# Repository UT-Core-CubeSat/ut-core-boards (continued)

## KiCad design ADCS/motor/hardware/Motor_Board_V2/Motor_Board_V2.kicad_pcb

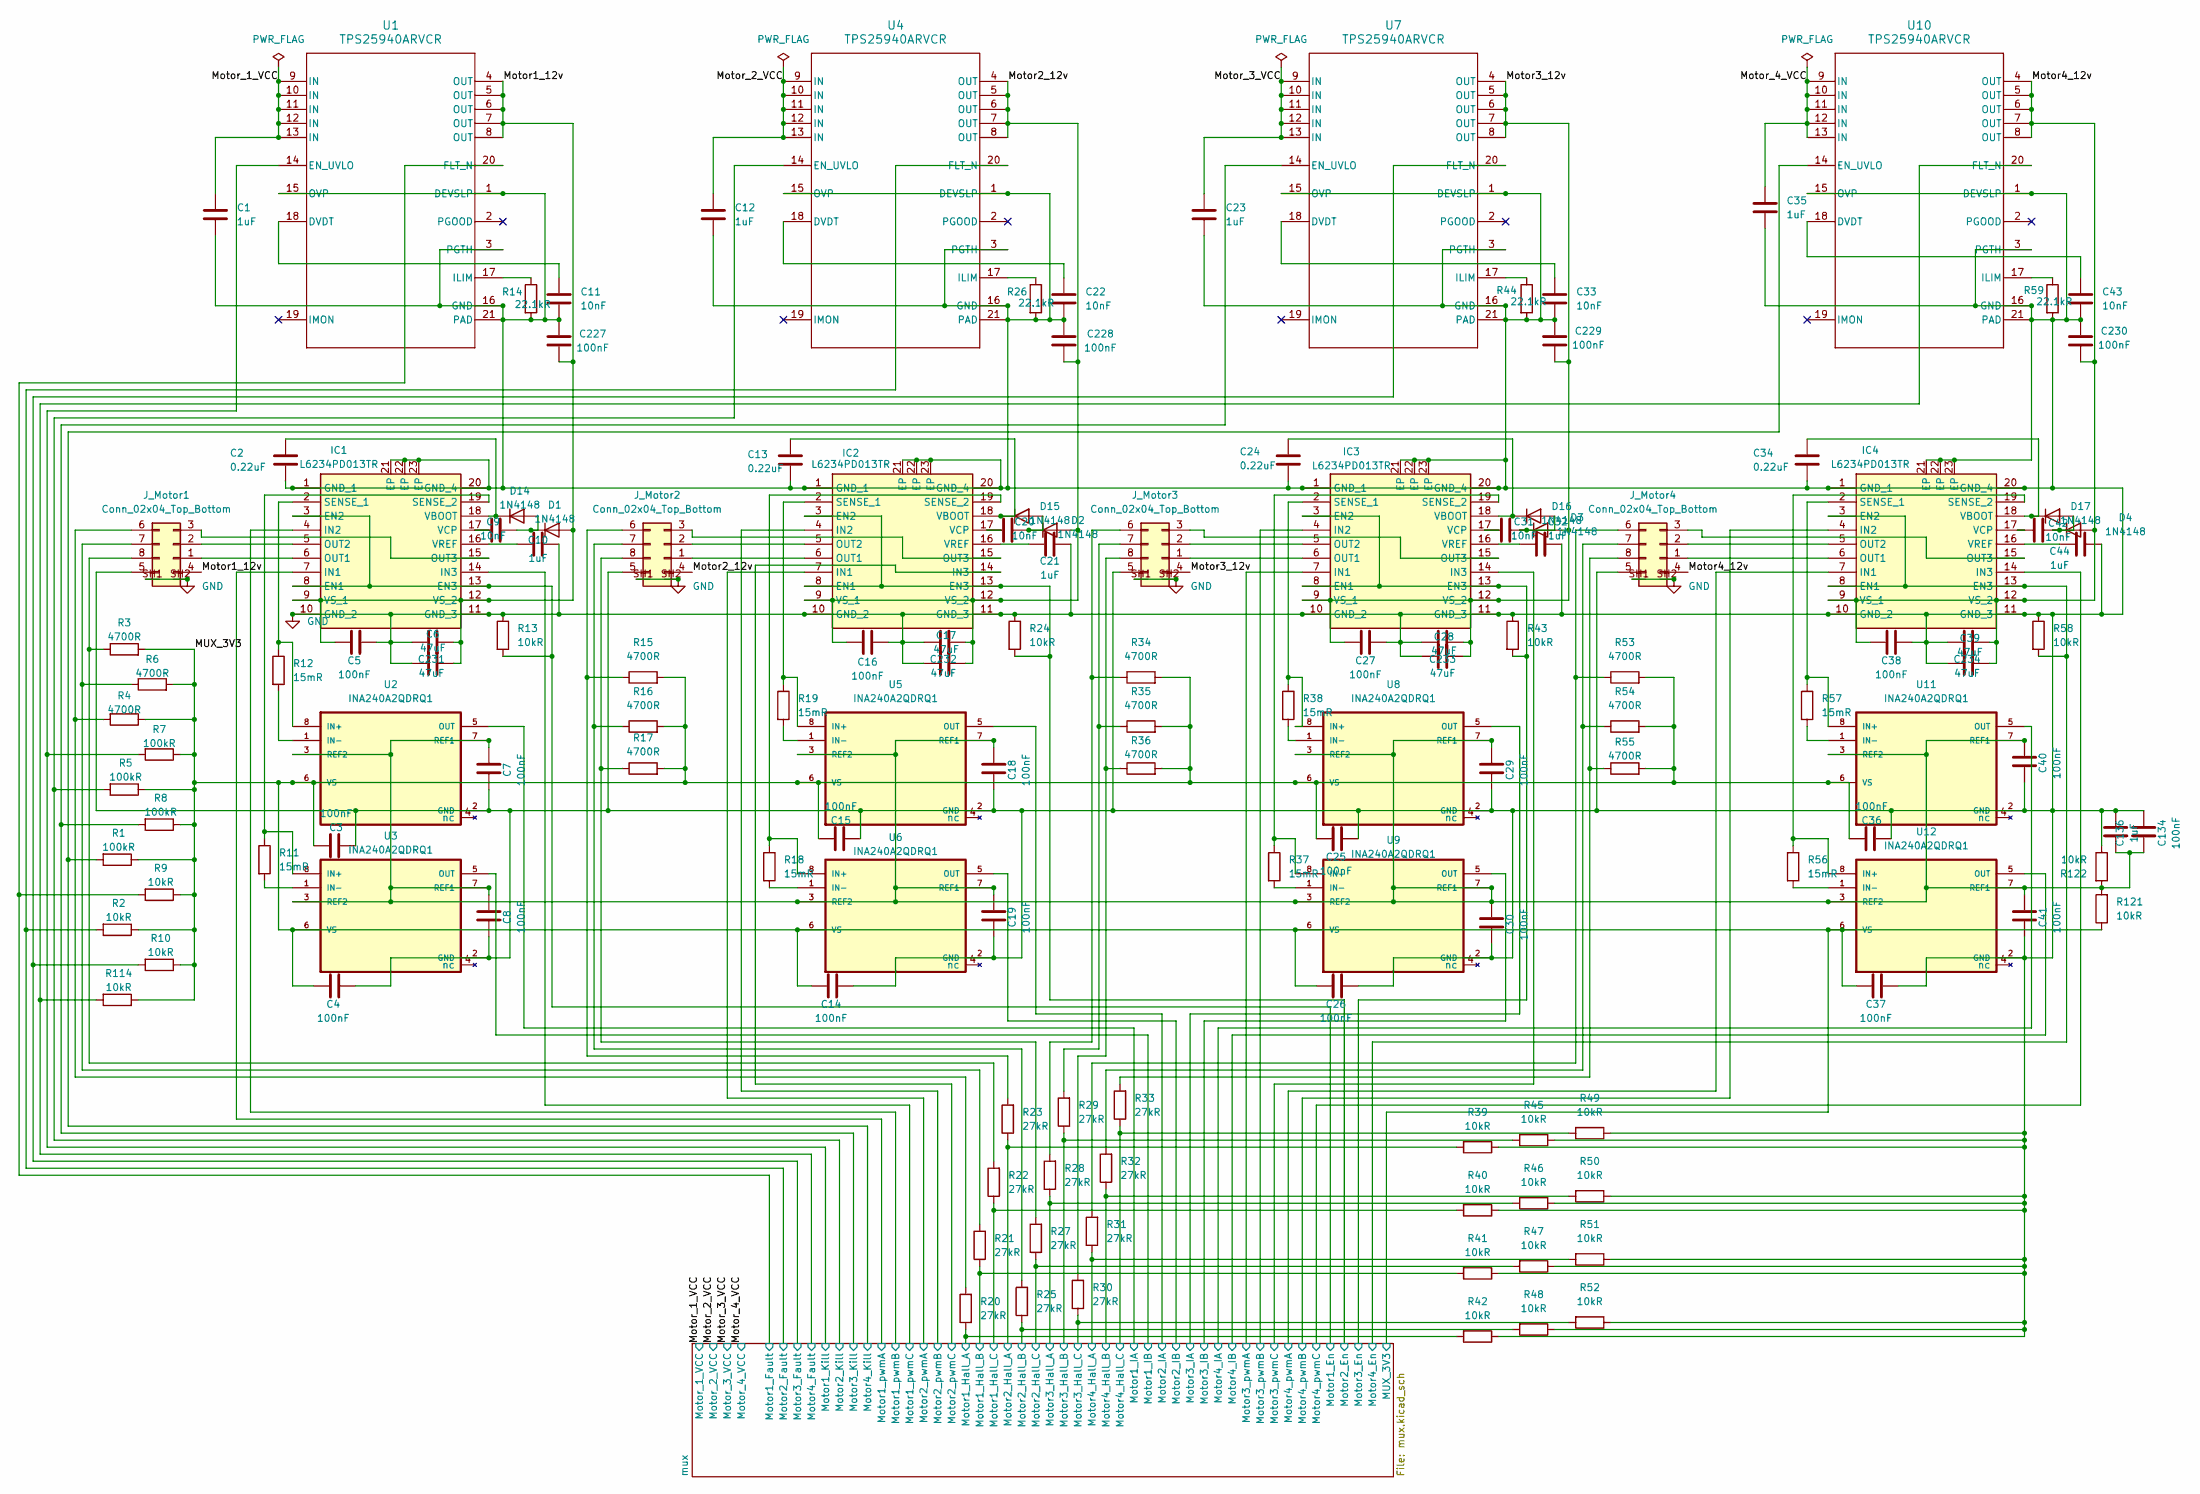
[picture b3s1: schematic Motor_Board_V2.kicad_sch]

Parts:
C1, C10, C12, C21, C23, C32, C35, C44, C136: 1uF; C_0603_1608Metric
C2, C13, C24, C34: 0.22uF; C_0603_1608Metric
C3, C4, C5, C7, C8, C14, C15, C16, C18, C19, C25, C26, C27, C29, C30, C36, C37, C38, C40, C41, C134, C227, C228, C229, C230: 100nF; C_0603_1608Metric
C6, C17, C28, C39, C231, C232, C233, C234: 47uF; C_1210_3225Metric
C9, C20, C31, C42: 10nF; C_0603_1608Metric_Pad1.08x0.95mm_HandSolder
C11, C22, C33, C43: 10nF; C_0603_1608Metric
D1, D2, D3, D4, D14, D15, D16, D17: 1N4148; D_SOD-523
IC1, IC2, IC3, IC4: L6234PD013TR; SOIC127P1420X360-21N; Manufacturer_Part_Number L6234PD; Mouser Part Number 511-L6234PD
J_Motor1, J_Motor2, J_Motor3, J_Motor4: Conn_02x04_Top_Bottom; AMPHENOL_SFW8S-2STME1LF
R1, R5, R7, R8: 100kR; R_0805_2012Metric
R2, R9, R10, R13, R24, R39, R40, R41, R42, R43, R45, R46, R47, R48, R49, R50, R51, R52, R58, R114, R121, R122: 10kR; R_0805_2012Metric
R3, R4, R6, R15, R16, R17, R34, R35, R36, R53, R54, R55: 4700R; R_0603_1608Metric
R11, R12, R18, R19, R37, R38, R56, R57: 15mR; R_2512_6332Metric
R14, R26, R44, R59: 22.1kR; R_0805_2012Metric
R20, R21, R22, R23, R25, R27, R28, R29, R30, R31, R32, R33: 27kR; R_0805_2012Metric
U1, U4, U7, U10: TPS25940ARVCR; RVC0020A
U2, U3, U5, U6, U8, U9, U11, U12: INA240A2QDRQ1; SOIC127P599X175-8N

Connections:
/MUX_3V3: C3.2, C4.1, C14.1, C15.2, C25.1, C26.1, C36.2, C37.1, R1.1, R2.1, R3.2, R4.1, R5.1, R6.2, R7.1, R8.1, R9.1, R10.1, R15.2, R16.2, R17.2, R34.2, R35.2, R36.2, R53.2, R54.2, R55.2, R114.1, R121.1, U2.6 (VS), U3.6 (VS), U5.6 (VS), U6.6 (VS), U8.6 (VS), U9.6 (VS), U11.6 (VS), U12.6 (VS); also elsewhere on the board
/Motor1_12v: C5.1, C6.1, C227.1, C231.1, D1.2 (A), IC1.9 (VS_1), IC1.12 (VS_2), J_Motor1.4 (Pin_8), U1.4 (OUT), U1.5 (OUT), U1.6 (OUT), U1.7 (OUT), U1.8 (OUT)
/Motor2_12v: C16.1, C17.1, C228.1, C232.1, D2.2 (A), IC2.9 (VS_1), IC2.12 (VS_2), J_Motor2.4 (Pin_8), U4.4 (OUT), U4.5 (OUT), U4.6 (OUT), U4.7 (OUT), U4.8 (OUT)
/Motor3_12v: C27.1, C28.1, C229.1, C233.1, D3.2 (A), IC3.9 (VS_1), IC3.12 (VS_2), J_Motor3.4 (Pin_8), U7.4 (OUT), U7.5 (OUT), U7.6 (OUT), U7.7 (OUT), U7.8 (OUT)
/Motor4_12v: C38.1, C39.1, C230.1, C234.1, D4.2 (A), IC4.9 (VS_1), IC4.12 (VS_2), J_Motor4.4 (Pin_8), U10.4 (OUT), U10.5 (OUT), U10.6 (OUT), U10.7 (OUT), U10.8 (OUT)
/Motor_1_VCC: C1.1, U1.9 (IN), U1.10 (IN), U1.11 (IN), U1.12 (IN), U1.13 (IN); also elsewhere on the board
/Motor_2_VCC: C12.1, U4.9 (IN), U4.10 (IN), U4.11 (IN), U4.12 (IN), U4.13 (IN); also elsewhere on the board
/Motor_3_VCC: C23.1, U7.9 (IN), U7.10 (IN), U7.11 (IN), U7.12 (IN), U7.13 (IN); also elsewhere on the board
/Motor_4_VCC: C35.1, U10.9 (IN), U10.10 (IN), U10.11 (IN), U10.12 (IN), U10.13 (IN); also elsewhere on the board
/mux/Motor1_En: IC1.3 (EN2), IC1.8 (EN1), IC1.13 (EN3), R13.2; also elsewhere on the board
/mux/Motor1_Fault: R9.2, U1.20 (FLT_N); also elsewhere on the board
/mux/Motor1_Hall_A: R20.1, R42.2; also elsewhere on the board
/mux/Motor1_Hall_B: R21.1, R41.2; also elsewhere on the board
/mux/Motor1_Hall_C: R22.1, R40.2; also elsewhere on the board
/mux/Motor1_IA: U2.5 (OUT); also elsewhere on the board
/mux/Motor1_IB: U3.5 (OUT); also elsewhere on the board
/mux/Motor1_Kill: R7.2, U1.14 (EN_UVLO); also elsewhere on the board
/mux/Motor1_pwmA: IC1.7 (IN1); also elsewhere on the board
/mux/Motor1_pwmB: IC1.4 (IN2); also elsewhere on the board
/mux/Motor1_pwmC: IC1.14 (IN3); also elsewhere on the board
/mux/Motor2_En: IC2.3 (EN2), IC2.8 (EN1), IC2.13 (EN3), R24.2; also elsewhere on the board
/mux/Motor2_Fault: R2.2, U4.20 (FLT_N); also elsewhere on the board
/mux/Motor2_Hall_A: R23.1, R39.2; also elsewhere on the board
/mux/Motor2_Hall_B: R25.1, R48.2; also elsewhere on the board
/mux/Motor2_Hall_C: R27.1, R47.2; also elsewhere on the board
/mux/Motor2_IA: U5.5 (OUT); also elsewhere on the board
/mux/Motor2_IB: U6.5 (OUT); also elsewhere on the board
/mux/Motor2_Kill: R5.2, U4.14 (EN_UVLO); also elsewhere on the board
/mux/Motor2_pwmA: IC2.7 (IN1); also elsewhere on the board
/mux/Motor2_pwmB: IC2.4 (IN2); also elsewhere on the board
/mux/Motor2_pwmC: IC2.14 (IN3); also elsewhere on the board
/mux/Motor3_En: IC3.3 (EN2), IC3.8 (EN1), IC3.13 (EN3), R43.2; also elsewhere on the board
/mux/Motor3_Fault: R10.2, U7.20 (FLT_N); also elsewhere on the board
/mux/Motor3_Hall_A: R28.1, R46.2; also elsewhere on the board
/mux/Motor3_Hall_B: R29.1, R45.2; also elsewhere on the board
/mux/Motor3_Hall_C: R30.1, R52.2; also elsewhere on the board
/mux/Motor3_IA: U8.5 (OUT); also elsewhere on the board
/mux/Motor3_IB: U9.5 (OUT); also elsewhere on the board
/mux/Motor3_Kill: R8.2, U7.14 (EN_UVLO); also elsewhere on the board
/mux/Motor3_pwmA: IC3.7 (IN1); also elsewhere on the board
/mux/Motor3_pwmB: IC3.4 (IN2); also elsewhere on the board
/mux/Motor3_pwmC: IC3.14 (IN3); also elsewhere on the board
/mux/Motor4_En: IC4.3 (EN2), IC4.8 (EN1), IC4.13 (EN3), R58.2; also elsewhere on the board
/mux/Motor4_Fault: R114.2, U10.20 (FLT_N); also elsewhere on the board
/mux/Motor4_Hall_A: R31.1, R51.2; also elsewhere on the board
/mux/Motor4_Hall_B: R32.1, R50.2; also elsewhere on the board
/mux/Motor4_Hall_C: R33.1, R49.2; also elsewhere on the board
/mux/Motor4_IA: U11.5 (OUT); also elsewhere on the board
/mux/Motor4_IB: U12.5 (OUT); also elsewhere on the board
/mux/Motor4_Kill: R1.2, U10.14 (EN_UVLO); also elsewhere on the board
/mux/Motor4_pwmA: IC4.7 (IN1); also elsewhere on the board
/mux/Motor4_pwmB: IC4.4 (IN2); also elsewhere on the board
/mux/Motor4_pwmC: IC4.14 (IN3); also elsewhere on the board
unnamed: C9.2, D1.1 (K), D14.2 (A)
unnamed: C2.1, D14.1 (K), IC1.18 (VBOOT)
unnamed: C20.2, D2.1 (K), D15.2 (A)
unnamed: C13.1, D15.1 (K), IC2.18 (VBOOT)
unnamed: C31.2, D3.1 (K), D16.2 (A)
unnamed: C24.1, D16.1 (K), IC3.18 (VBOOT)
unnamed: C42.2, D4.1 (K), D17.2 (A)
unnamed: C34.1, D17.1 (K), IC4.18 (VBOOT)
unnamed: IC1.6 (OUT1), J_Motor1.1 (Pin_7)
unnamed: IC1.5 (OUT2), J_Motor1.2 (Pin_6)
unnamed: IC1.15 (OUT3), J_Motor1.3 (Pin_5)
unnamed: IC1.2 (SENSE_1), R12.1, U2.8 (IN+)
unnamed: IC1.19 (SENSE_2), R11.1, U3.8 (IN+)
unnamed: C9.1, IC1.17 (VCP)
unnamed: C10.1, IC1.16 (VREF)
unnamed: IC2.6 (OUT1), J_Motor2.1 (Pin_7)
unnamed: IC2.5 (OUT2), J_Motor2.2 (Pin_6)
unnamed: IC2.15 (OUT3), J_Motor2.3 (Pin_5)
unnamed: IC2.2 (SENSE_1), R19.1, U5.8 (IN+)
unnamed: IC2.19 (SENSE_2), R18.1, U6.8 (IN+)
unnamed: C20.1, IC2.17 (VCP)
unnamed: C21.1, IC2.16 (VREF)
unnamed: IC3.6 (OUT1), J_Motor3.1 (Pin_7)
unnamed: IC3.5 (OUT2), J_Motor3.2 (Pin_6)
unnamed: IC3.15 (OUT3), J_Motor3.3 (Pin_5)
unnamed: IC3.2 (SENSE_1), R38.1, U8.8 (IN+)
unnamed: IC3.19 (SENSE_2), R37.1, U9.8 (IN+)
unnamed: C31.1, IC3.17 (VCP)
unnamed: C32.1, IC3.16 (VREF)
unnamed: IC4.6 (OUT1), J_Motor4.1 (Pin_7)
unnamed: IC4.5 (OUT2), J_Motor4.2 (Pin_6)
unnamed: IC4.15 (OUT3), J_Motor4.3 (Pin_5)
unnamed: IC4.2 (SENSE_1), R57.1, U11.8 (IN+)
unnamed: IC4.19 (SENSE_2), R56.1, U12.8 (IN+)
unnamed: C42.1, IC4.17 (VCP)
unnamed: C44.1, IC4.16 (VREF)
unnamed: J_Motor1.6 (Pin_1), R4.2, R20.2
unnamed: J_Motor1.7 (Pin_2), R6.1, R21.2
unnamed: J_Motor1.8 (Pin_3), R3.1, R22.2
unnamed: J_Motor2.6 (Pin_1), R15.1, R23.2
unnamed: J_Motor2.7 (Pin_2), R16.1, R25.2
unnamed: J_Motor2.8 (Pin_3), R17.1, R27.2
unnamed: J_Motor3.6 (Pin_1), R28.2, R34.1
unnamed: J_Motor3.7 (Pin_2), R29.2, R35.1
unnamed: J_Motor3.8 (Pin_3), R30.2, R36.1
unnamed: J_Motor4.6 (Pin_1), R31.2, R53.1
unnamed: J_Motor4.7 (Pin_2), R32.2, R54.1
unnamed: J_Motor4.8 (Pin_3), R33.2, R55.1
unnamed: C11.1, U1.18 (DVDT)
unnamed: R14.1, U1.17 (ILIM)
unnamed: R12.2, U2.1 (IN-)
unnamed: R11.2, U3.1 (IN-)
unnamed: C22.1, U4.18 (DVDT)
unnamed: R26.1, U4.17 (ILIM)
unnamed: R19.2, U5.1 (IN-)
unnamed: R18.2, U6.1 (IN-)
unnamed: C33.1, U7.18 (DVDT)
unnamed: R44.1, U7.17 (ILIM)
unnamed: R38.2, U8.1 (IN-)
unnamed: R37.2, U9.1 (IN-)
unnamed: C43.1, U10.18 (DVDT)
unnamed: R59.1, U10.17 (ILIM)
unnamed: R57.2, U11.1 (IN-)
unnamed: C7.2, C8.2, C18.2, C19.2, C29.2, C30.2, C40.2, C41.2, C134.1, C136.1, R121.2, R122.2, U2.3 (REF2), U2.7 (REF1), U3.3 (REF2), U3.7 (REF1), U5.3 (REF2), U5.7 (REF1), U6.3 (REF2), U6.7 (REF1), U8.3 (REF2), U8.7 (REF1), U9.3 (REF2), U9.7 (REF1), U11.3 (REF2), U11.7 (REF1), U12.3 (REF2), U12.7 (REF1)
unnamed: R56.2, U12.1 (IN-)

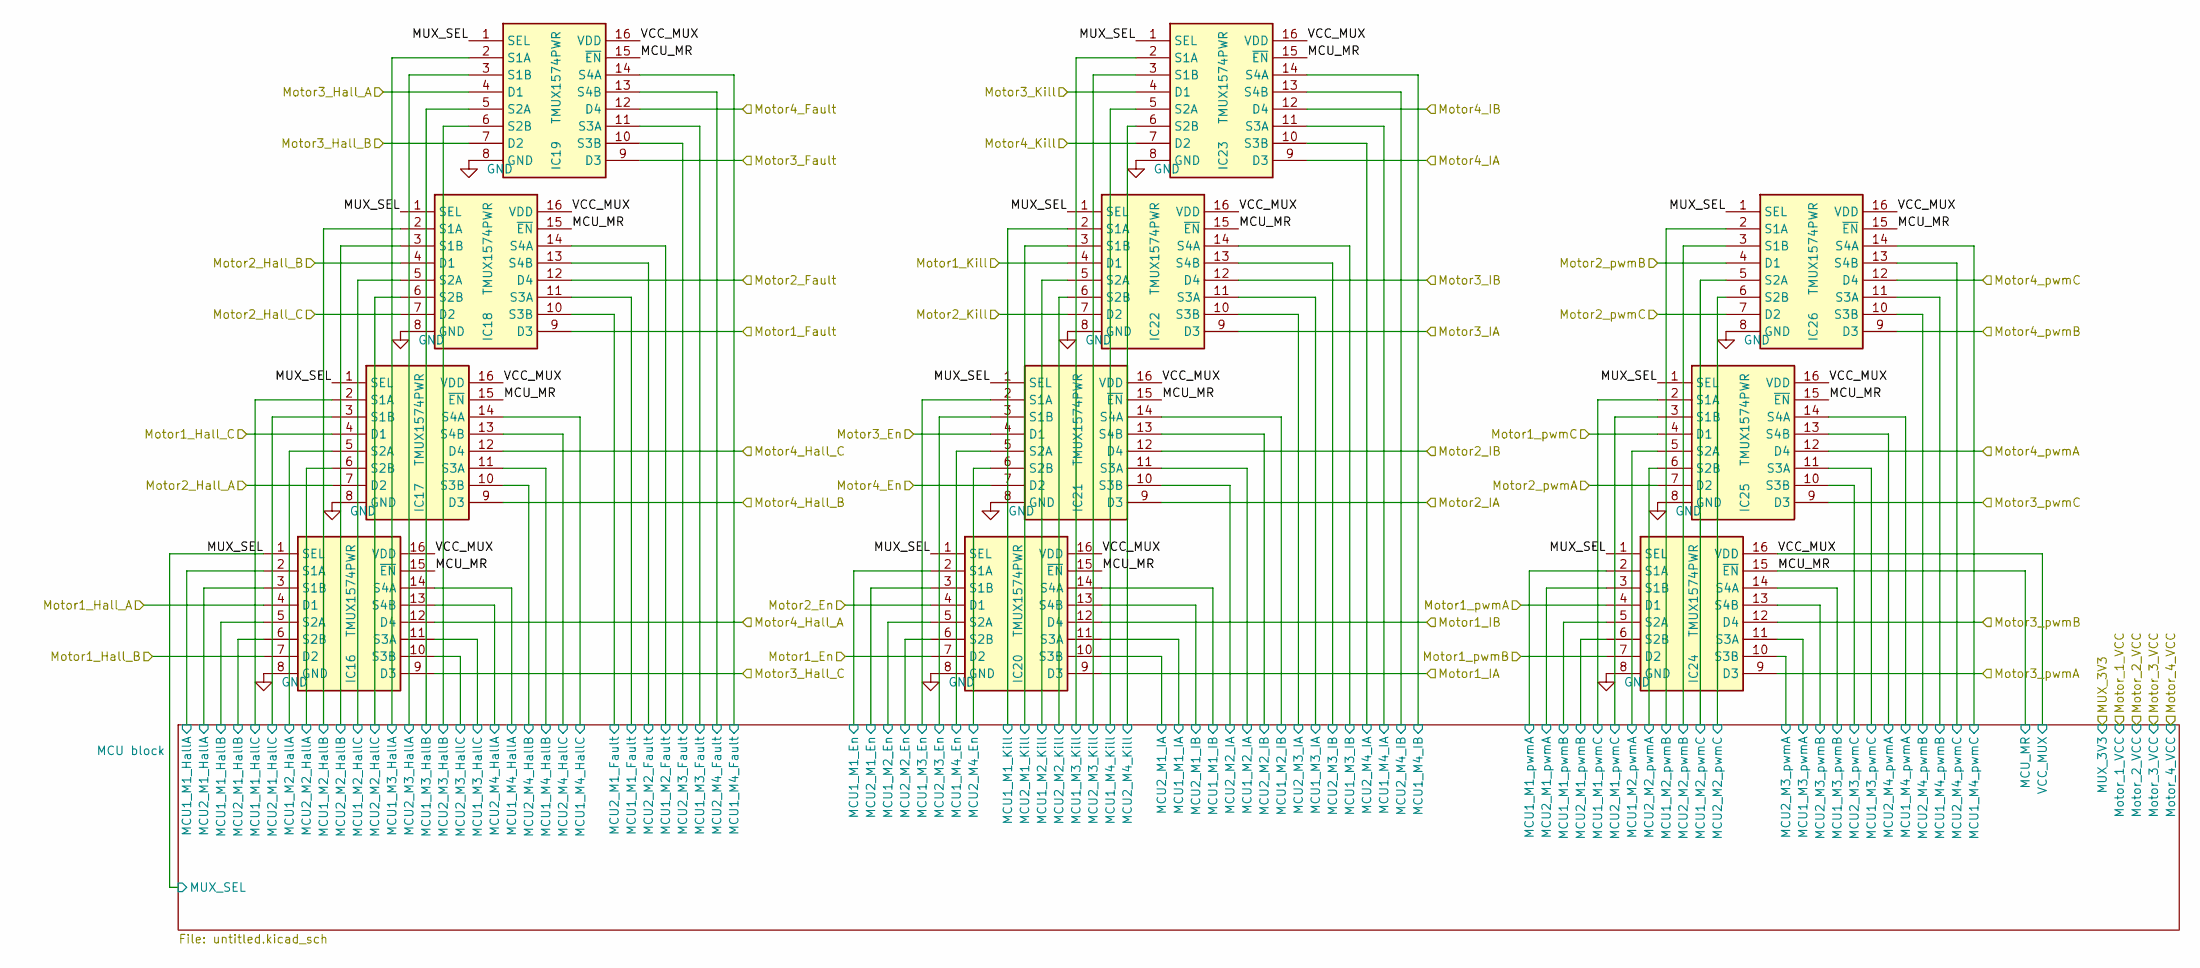
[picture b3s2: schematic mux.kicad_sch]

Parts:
IC16, IC17, IC18, IC19, IC20, IC21, IC22, IC23, IC24, IC25, IC26: TMUX1574PWR; Mouser Part Number 595-TMUX1574PWR

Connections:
/mux/MCU block/MCU1_M1_En: IC20.3 (S1B); also elsewhere on the board
/mux/MCU block/MCU1_M1_Fault: IC18.11 (S3A); also elsewhere on the board
/mux/MCU block/MCU1_M1_HallA: IC16.2 (S1A); also elsewhere on the board
/mux/MCU block/MCU1_M1_HallB: IC16.5 (S2A); also elsewhere on the board
/mux/MCU block/MCU1_M1_HallC: IC17.2 (S1A); also elsewhere on the board
/mux/MCU block/MCU1_M1_IA: IC20.10 (S3B); also elsewhere on the board
/mux/MCU block/MCU1_M1_IB: IC20.13 (S4B); also elsewhere on the board
/mux/MCU block/MCU1_M1_Kill: IC22.3 (S1B); also elsewhere on the board
/mux/MCU block/MCU1_M1_pwmA: IC24.2 (S1A); also elsewhere on the board
/mux/MCU block/MCU1_M1_pwmB: IC24.5 (S2A); also elsewhere on the board
/mux/MCU block/MCU1_M1_pwmC: IC25.2 (S1A); also elsewhere on the board
/mux/MCU block/MCU1_M2_En: IC20.6 (S2B); also elsewhere on the board
/mux/MCU block/MCU1_M2_Fault: IC18.14 (S4A); also elsewhere on the board
/mux/MCU block/MCU1_M2_HallA: IC17.5 (S2A); also elsewhere on the board
/mux/MCU block/MCU1_M2_HallB: IC18.2 (S1A); also elsewhere on the board
/mux/MCU block/MCU1_M2_HallC: IC18.5 (S2A); also elsewhere on the board
/mux/MCU block/MCU1_M2_IA: IC21.10 (S3B); also elsewhere on the board
/mux/MCU block/MCU1_M2_IB: IC21.13 (S4B); also elsewhere on the board
/mux/MCU block/MCU1_M2_Kill: IC22.6 (S2B); also elsewhere on the board
/mux/MCU block/MCU1_M2_pwmA: IC25.5 (S2A); also elsewhere on the board
/mux/MCU block/MCU1_M2_pwmB: IC26.2 (S1A); also elsewhere on the board
/mux/MCU block/MCU1_M2_pwmC: IC26.5 (S2A); also elsewhere on the board
/mux/MCU block/MCU1_M3_En: IC21.3 (S1B); also elsewhere on the board
/mux/MCU block/MCU1_M3_Fault: IC19.11 (S3A); also elsewhere on the board
/mux/MCU block/MCU1_M3_HallA: IC19.2 (S1A); also elsewhere on the board
/mux/MCU block/MCU1_M3_HallB: IC19.5 (S2A); also elsewhere on the board
/mux/MCU block/MCU1_M3_HallC: IC16.10 (S3B); also elsewhere on the board
/mux/MCU block/MCU1_M3_IA: IC22.10 (S3B); also elsewhere on the board
/mux/MCU block/MCU1_M3_IB: IC22.13 (S4B); also elsewhere on the board
/mux/MCU block/MCU1_M3_Kill: IC23.3 (S1B); also elsewhere on the board
/mux/MCU block/MCU1_M3_pwmA: IC24.10 (S3B); also elsewhere on the board
/mux/MCU block/MCU1_M3_pwmB: IC24.13 (S4B); also elsewhere on the board
/mux/MCU block/MCU1_M3_pwmC: IC25.10 (S3B); also elsewhere on the board
/mux/MCU block/MCU1_M4_En: IC21.6 (S2B); also elsewhere on the board
/mux/MCU block/MCU1_M4_Fault: IC19.14 (S4A); also elsewhere on the board
/mux/MCU block/MCU1_M4_HallA: IC16.13 (S4B); also elsewhere on the board
/mux/MCU block/MCU1_M4_HallB: IC17.10 (S3B); also elsewhere on the board
/mux/MCU block/MCU1_M4_HallC: IC17.13 (S4B); also elsewhere on the board
/mux/MCU block/MCU1_M4_IA: IC23.10 (S3B); also elsewhere on the board
/mux/MCU block/MCU1_M4_IB: IC23.13 (S4B); also elsewhere on the board
/mux/MCU block/MCU1_M4_Kill: IC23.6 (S2B); also elsewhere on the board
/mux/MCU block/MCU1_M4_pwmA: IC25.13 (S4B); also elsewhere on the board
/mux/MCU block/MCU1_M4_pwmB: IC26.10 (S3B); also elsewhere on the board
/mux/MCU block/MCU1_M4_pwmC: IC26.13 (S4B); also elsewhere on the board
/mux/MCU block/MCU2_M1_En: IC20.2 (S1A); also elsewhere on the board
/mux/MCU block/MCU2_M1_Fault: IC18.10 (S3B); also elsewhere on the board
/mux/MCU block/MCU2_M1_HallA: IC16.3 (S1B); also elsewhere on the board
/mux/MCU block/MCU2_M1_HallB: IC16.6 (S2B); also elsewhere on the board
/mux/MCU block/MCU2_M1_HallC: IC17.3 (S1B); also elsewhere on the board
/mux/MCU block/MCU2_M1_IA: IC20.11 (S3A); also elsewhere on the board
/mux/MCU block/MCU2_M1_IB: IC20.14 (S4A); also elsewhere on the board
/mux/MCU block/MCU2_M1_Kill: IC22.2 (S1A); also elsewhere on the board
/mux/MCU block/MCU2_M1_pwmA: IC24.3 (S1B); also elsewhere on the board
/mux/MCU block/MCU2_M1_pwmB: IC24.6 (S2B); also elsewhere on the board
/mux/MCU block/MCU2_M1_pwmC: IC25.3 (S1B); also elsewhere on the board
/mux/MCU block/MCU2_M2_En: IC20.5 (S2A); also elsewhere on the board
/mux/MCU block/MCU2_M2_Fault: IC18.13 (S4B); also elsewhere on the board
/mux/MCU block/MCU2_M2_HallA: IC17.6 (S2B); also elsewhere on the board
/mux/MCU block/MCU2_M2_HallB: IC18.3 (S1B); also elsewhere on the board
/mux/MCU block/MCU2_M2_HallC: IC18.6 (S2B); also elsewhere on the board
/mux/MCU block/MCU2_M2_IA: IC21.11 (S3A); also elsewhere on the board
/mux/MCU block/MCU2_M2_IB: IC21.14 (S4A); also elsewhere on the board
/mux/MCU block/MCU2_M2_Kill: IC22.5 (S2A); also elsewhere on the board
/mux/MCU block/MCU2_M2_pwmA: IC25.6 (S2B); also elsewhere on the board
/mux/MCU block/MCU2_M2_pwmB: IC26.3 (S1B); also elsewhere on the board
/mux/MCU block/MCU2_M2_pwmC: IC26.6 (S2B); also elsewhere on the board
/mux/MCU block/MCU2_M3_En: IC21.2 (S1A); also elsewhere on the board
/mux/MCU block/MCU2_M3_Fault: IC19.10 (S3B); also elsewhere on the board
/mux/MCU block/MCU2_M3_HallA: IC19.3 (S1B); also elsewhere on the board
/mux/MCU block/MCU2_M3_HallB: IC19.6 (S2B); also elsewhere on the board
/mux/MCU block/MCU2_M3_HallC: IC16.11 (S3A); also elsewhere on the board
/mux/MCU block/MCU2_M3_IA: IC22.11 (S3A); also elsewhere on the board
/mux/MCU block/MCU2_M3_IB: IC22.14 (S4A); also elsewhere on the board
/mux/MCU block/MCU2_M3_Kill: IC23.2 (S1A); also elsewhere on the board
/mux/MCU block/MCU2_M3_pwmA: IC24.11 (S3A); also elsewhere on the board
/mux/MCU block/MCU2_M3_pwmB: IC24.14 (S4A); also elsewhere on the board
/mux/MCU block/MCU2_M3_pwmC: IC25.11 (S3A); also elsewhere on the board
/mux/MCU block/MCU2_M4_En: IC21.5 (S2A); also elsewhere on the board
/mux/MCU block/MCU2_M4_Fault: IC19.13 (S4B); also elsewhere on the board
/mux/MCU block/MCU2_M4_HallA: IC16.14 (S4A); also elsewhere on the board
/mux/MCU block/MCU2_M4_HallB: IC17.11 (S3A); also elsewhere on the board
/mux/MCU block/MCU2_M4_HallC: IC17.14 (S4A); also elsewhere on the board
/mux/MCU block/MCU2_M4_IA: IC23.11 (S3A); also elsewhere on the board
/mux/MCU block/MCU2_M4_IB: IC23.14 (S4A); also elsewhere on the board
/mux/MCU block/MCU2_M4_Kill: IC23.5 (S2A); also elsewhere on the board
/mux/MCU block/MCU2_M4_pwmA: IC25.14 (S4A); also elsewhere on the board
/mux/MCU block/MCU2_M4_pwmB: IC26.11 (S3A); also elsewhere on the board
/mux/MCU block/MCU2_M4_pwmC: IC26.14 (S4A); also elsewhere on the board
/mux/MCU_MR: IC16.15 (~EN), IC17.15 (~EN), IC18.15 (~EN), IC19.15 (~EN), IC20.15 (~EN), IC21.15 (~EN), IC22.15 (~EN), IC23.15 (~EN), IC24.15 (~EN), IC25.15 (~EN), IC26.15 (~EN); also elsewhere on the board
/mux/MUX_SEL: IC16.1 (SEL), IC17.1 (SEL), IC18.1 (SEL), IC19.1 (SEL), IC20.1 (SEL), IC21.1 (SEL), IC22.1 (SEL), IC23.1 (SEL), IC24.1 (SEL), IC25.1 (SEL), IC26.1 (SEL); also elsewhere on the board
/mux/Motor1_En: IC20.7 (D2); also elsewhere on the board
/mux/Motor1_Fault: IC18.9 (D3); also elsewhere on the board
/mux/Motor1_Hall_A: IC16.4 (D1); also elsewhere on the board
/mux/Motor1_Hall_B: IC16.7 (D2); also elsewhere on the board
/mux/Motor1_Hall_C: IC17.4 (D1); also elsewhere on the board
/mux/Motor1_IA: IC20.9 (D3); also elsewhere on the board
/mux/Motor1_IB: IC20.12 (D4); also elsewhere on the board
/mux/Motor1_Kill: IC22.4 (D1); also elsewhere on the board
/mux/Motor1_pwmA: IC24.4 (D1); also elsewhere on the board
/mux/Motor1_pwmB: IC24.7 (D2); also elsewhere on the board
/mux/Motor1_pwmC: IC25.4 (D1); also elsewhere on the board
/mux/Motor2_En: IC20.4 (D1); also elsewhere on the board
/mux/Motor2_Fault: IC18.12 (D4); also elsewhere on the board
/mux/Motor2_Hall_A: IC17.7 (D2); also elsewhere on the board
/mux/Motor2_Hall_B: IC18.4 (D1); also elsewhere on the board
/mux/Motor2_Hall_C: IC18.7 (D2); also elsewhere on the board
/mux/Motor2_IA: IC21.9 (D3); also elsewhere on the board
/mux/Motor2_IB: IC21.12 (D4); also elsewhere on the board
/mux/Motor2_Kill: IC22.7 (D2); also elsewhere on the board
/mux/Motor2_pwmA: IC25.7 (D2); also elsewhere on the board
/mux/Motor2_pwmB: IC26.4 (D1); also elsewhere on the board
/mux/Motor2_pwmC: IC26.7 (D2); also elsewhere on the board
/mux/Motor3_En: IC21.4 (D1); also elsewhere on the board
/mux/Motor3_Fault: IC19.9 (D3); also elsewhere on the board
/mux/Motor3_Hall_A: IC19.4 (D1); also elsewhere on the board
/mux/Motor3_Hall_B: IC19.7 (D2); also elsewhere on the board
/mux/Motor3_Hall_C: IC16.9 (D3); also elsewhere on the board
/mux/Motor3_IA: IC22.9 (D3); also elsewhere on the board
/mux/Motor3_IB: IC22.12 (D4); also elsewhere on the board
/mux/Motor3_Kill: IC23.4 (D1); also elsewhere on the board
/mux/Motor3_pwmA: IC24.9 (D3); also elsewhere on the board
/mux/Motor3_pwmB: IC24.12 (D4); also elsewhere on the board
/mux/Motor3_pwmC: IC25.9 (D3); also elsewhere on the board
/mux/Motor4_En: IC21.7 (D2); also elsewhere on the board
/mux/Motor4_Fault: IC19.12 (D4); also elsewhere on the board
/mux/Motor4_Hall_A: IC16.12 (D4); also elsewhere on the board
/mux/Motor4_Hall_B: IC17.9 (D3); also elsewhere on the board
/mux/Motor4_Hall_C: IC17.12 (D4); also elsewhere on the board
/mux/Motor4_IA: IC23.9 (D3); also elsewhere on the board
/mux/Motor4_IB: IC23.12 (D4); also elsewhere on the board
/mux/Motor4_Kill: IC23.7 (D2); also elsewhere on the board
/mux/Motor4_pwmA: IC25.12 (D4); also elsewhere on the board
/mux/Motor4_pwmB: IC26.9 (D3); also elsewhere on the board
/mux/Motor4_pwmC: IC26.12 (D4); also elsewhere on the board
/mux/VCC_MUX: IC16.16 (VDD), IC17.16 (VDD), IC18.16 (VDD), IC19.16 (VDD), IC20.16 (VDD), IC21.16 (VDD), IC22.16 (VDD), IC23.16 (VDD), IC24.16 (VDD), IC25.16 (VDD), IC26.16 (VDD); also elsewhere on the board
